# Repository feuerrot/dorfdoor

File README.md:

# Türsteuerung
Can haz digitale Türsteuerung mit verschiedenen Inputs und Statusleds und
foo? Ja!

Die [Tür des Chaosdorf](https://wiki.chaosdorf.de/Chaosdoor) hat einen 
eingebauten Motor von Fuhr - den Multitronic 881 und da alle Funkanwendungen
(insbesondere der Funk-Fingerabdrucksensor) auf unbekannter Technik basieren
und damit erstmal als für einen Hackerspace ungeeignet gelten, muss man das
natürlich selber bauen.

## History
v1 umfasste eine Lochrasterplatine mit AVR ATMega8, der über Optokoppler den
Potentialfreien Eingang des Türmotors ansteuerte. Ein Problem war unter
anderem, dass der komplette Öffnungs- und Schließvorgang incl. Verriegeln
dazu führte, dass nach gerade mal 3 Jahren ein Zahnrad brach.

Die aktuelle v2 mit 'lag halt rum' AVR ATMega88PA trennt eigentliche
Steuerung und Boardinterface auf zwei Platinen auf. Der Mikrocontroller ist
zusammen mit der verbundenen Seagate Dockstar und passendem Netzteil für
alles und Tür in einem Gehäuse. Die Ansteuerung der Tür und das damit
verbundene Problem bleibt bestehen.

[@penma](https://github.com/penma) hat aber dankenswerterweise das
Protokoll der Tür im für unseren Zweck ausreichenden Maße reverse
engineered, um die gewünschte Tagesfallenfunktion auch ohne Zusatzplatine
für wahrscheinlich mehrere hunderte Euro zu erlangen.
Bei v2 wird dafür der Optokoppler für die Tagesfalle genutzt.

## Schaltplan

### μC-Platine

### IO-Platine

## Layout

### μC-Platine

### IO-Platine

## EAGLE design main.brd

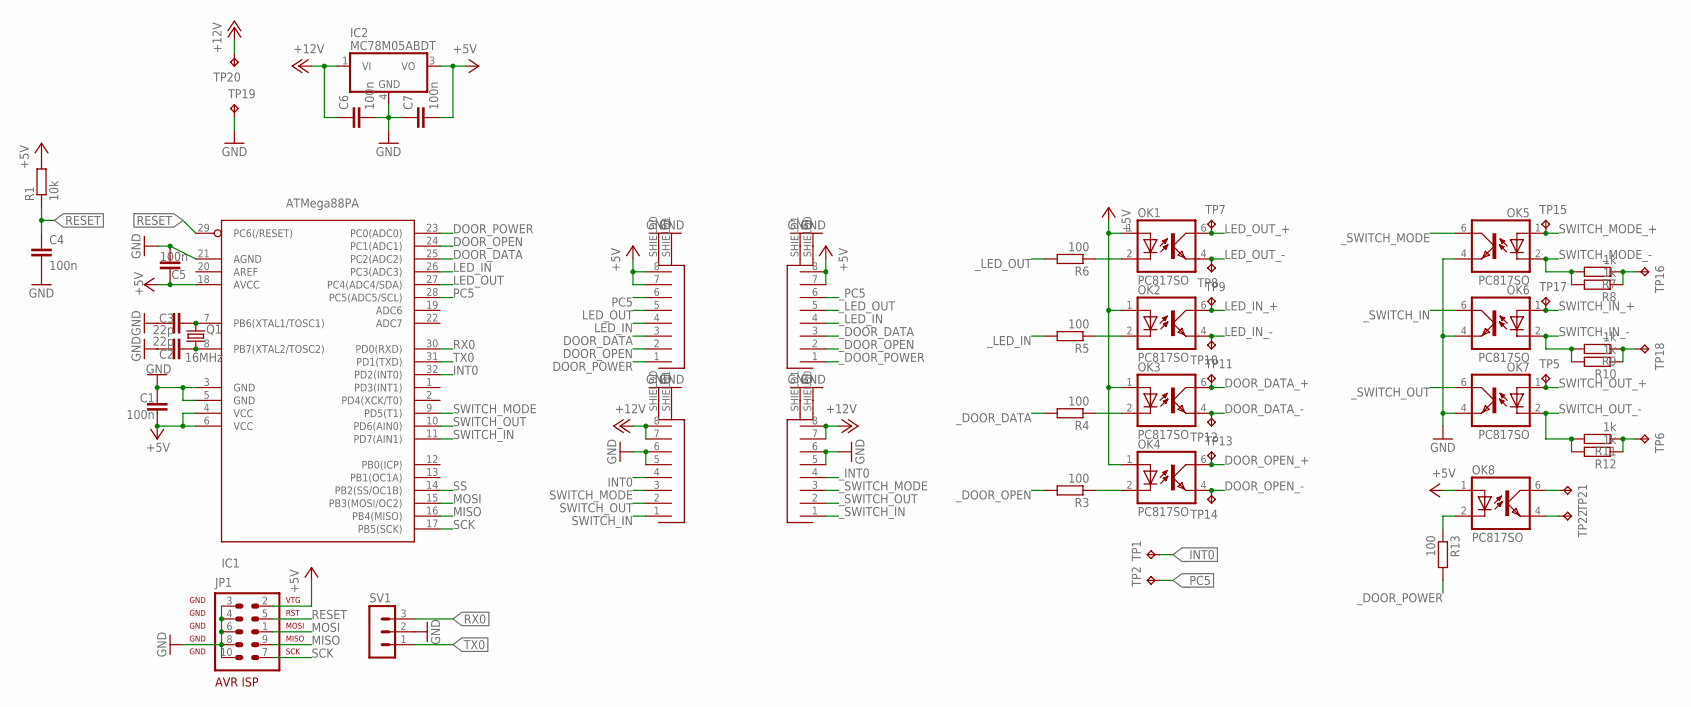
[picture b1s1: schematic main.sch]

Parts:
C1, C4, C5, C6, C7: 100n; C0805
C2, C3: 22p; C0805
CON1, CON1_, CON2, CON2_: 451000
IC1: ATMega88PA; TQFP32-08
IC2: MC78M05ABDT; DPACK_3
JP1: AVR-ISP-10
OK1, OK2, OK3, OK4, OK5, OK6, OK7, OK8: PC817SO; SO4
Q1: 16MHz; MQ
R1: 10k; M0805
R3, R4, R5, R6, R13: 100; M0805
R7, R8, R9, R10, R11, R12: 1k; M0805
SV1: MA03-1
TP1, TP2, TP5, TP6, TP7, TP8, TP9, TP10, TP11, TP12, TP13, TP14, TP15, TP16, TP17, TP18, TP19, TP20, TP21, TP22: TPTP20SQ; TP20SQ

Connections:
+5V: C1.1, C5.1, C7.2, CON2.7, CON2.8, CON2_.7, CON2_.8, IC1.4 (VCC), IC1.6 (VCC), IC1.18 (AVCC), IC2.3 (VO), JP1.2, OK1.1 (A), OK2.1 (A), OK3.1 (A), OK4.1 (A), OK8.1 (A), R1.2
+12V: C6.1, CON1.7, CON1.8, CON1_.7, CON1_.8, IC2.1 (VI), TP20.TP
DOOR_DATA: CON2.3, IC1.25 (PC2(ADC2))
DOOR_DATA_+: OK3.6 (COL), TP11.TP
DOOR_DATA_-: OK3.4 (EMIT), TP12.TP
DOOR_OPEN: CON2.2, IC1.24 (PC1(ADC1))
DOOR_OPEN_+: OK4.6 (COL), TP13.TP
DOOR_OPEN_-: OK4.4 (EMIT), TP14.TP
DOOR_POWER: CON2.1, IC1.23 (PC0(ADC0))
GND: C1.2, C2.1, C3.1, C4.2, C5.2, C6.2, C7.1, CON1.5, CON1.6, CON1.SHIELD0, CON1.SHIELD1, CON1_.5, CON1_.6, CON1_.SHIELD0, CON1_.SHIELD1, CON2.SHIELD0, CON2.SHIELD1, CON2_.SHIELD0, CON2_.SHIELD1, IC1.3 (GND), IC1.5 (GND), IC1.21 (AGND), IC2.4 (GND), JP1.3, JP1.4, JP1.6, JP1.8, JP1.10, OK5.4 (EMIT), OK6.4 (EMIT), OK7.4 (EMIT), SV1.2, TP19.TP
INT0: CON1.4, IC1.32 (PD2(INT0))
LED_IN: CON2.4, IC1.26 (PC3(ADC3))
LED_IN_+: OK2.6 (COL), TP9.TP
LED_IN_-: OK2.4 (EMIT), TP10.TP
LED_OUT: CON2.5, IC1.27 (PC4(ADC4/SDA))
LED_OUT_+: OK1.6 (COL), TP7.TP
LED_OUT_-: OK1.4 (EMIT), TP8.TP
MISO: IC1.16 (PB4(MISO)), JP1.9
MOSI: IC1.15 (PB3(MOSI/OC2)), JP1.1
unnamed: OK8.2 (C), R13.1
unnamed: OK4.2 (C), R3.1
unnamed: C3.2, IC1.7 (PB6(XTAL1/TOSC1)), Q1.P3 (2)
unnamed: C2.2, IC1.8 (PB7(XTAL2/TOSC2)), Q1.P1 (1)
unnamed: OK3.2 (C), R4.1
unnamed: OK2.2 (C), R5.1
unnamed: OK1.2 (C), R6.1
unnamed: R7.1, R8.1, TP16.TP
unnamed: R11.1, R12.1, TP6.TP
unnamed: R9.1, R10.1, TP18.TP
unnamed: OK8.6 (COL), TP21.TP
unnamed: OK8.4 (EMIT), TP22.TP
PC5: CON2.6, IC1.28 (PC5(ADC5/SCL))
RESET: C4.1, IC1.29 (PC6(/RESET)), JP1.5, R1.1
RX0: IC1.30 (PD0(RXD)), SV1.3
SCK: IC1.17 (PB5(SCK)), JP1.7
SS: IC1.14 (PB2(SS/OC1B))
SWITCH_IN: CON1.1, IC1.11 (PD7(AIN1))
SWITCH_IN_+: OK6.1 (A), TP17.TP
SWITCH_IN_-: OK6.2 (C), R9.2, R10.2
SWITCH_MODE: CON1.3, IC1.9 (PD5(T1))
SWITCH_MODE_+: OK5.1 (A), TP15.TP
SWITCH_MODE_-: OK5.2 (C), R7.2, R8.2
SWITCH_OUT: CON1.2, IC1.10 (PD6(AIN0))
SWITCH_OUT_+: OK7.1 (A), TP5.TP
SWITCH_OUT_-: OK7.2 (C), R11.2, R12.2
TX0: IC1.31 (PD1(TXD)), SV1.1
_DOOR_DATA: CON2_.3, R4.2
_DOOR_OPEN: CON2_.2, R3.2
_DOOR_POWER: CON2_.1, R13.2
_INT0: CON1_.4, TP1.TP
_LED_IN: CON2_.4, R5.2
_LED_OUT: CON2_.5, R6.2
_PC5: CON2_.6, TP2.TP
_SWITCH_IN: CON1_.1, OK6.6 (COL)
_SWITCH_MODE: CON1_.3, OK5.6 (COL)
_SWITCH_OUT: CON1_.2, OK7.6 (COL)

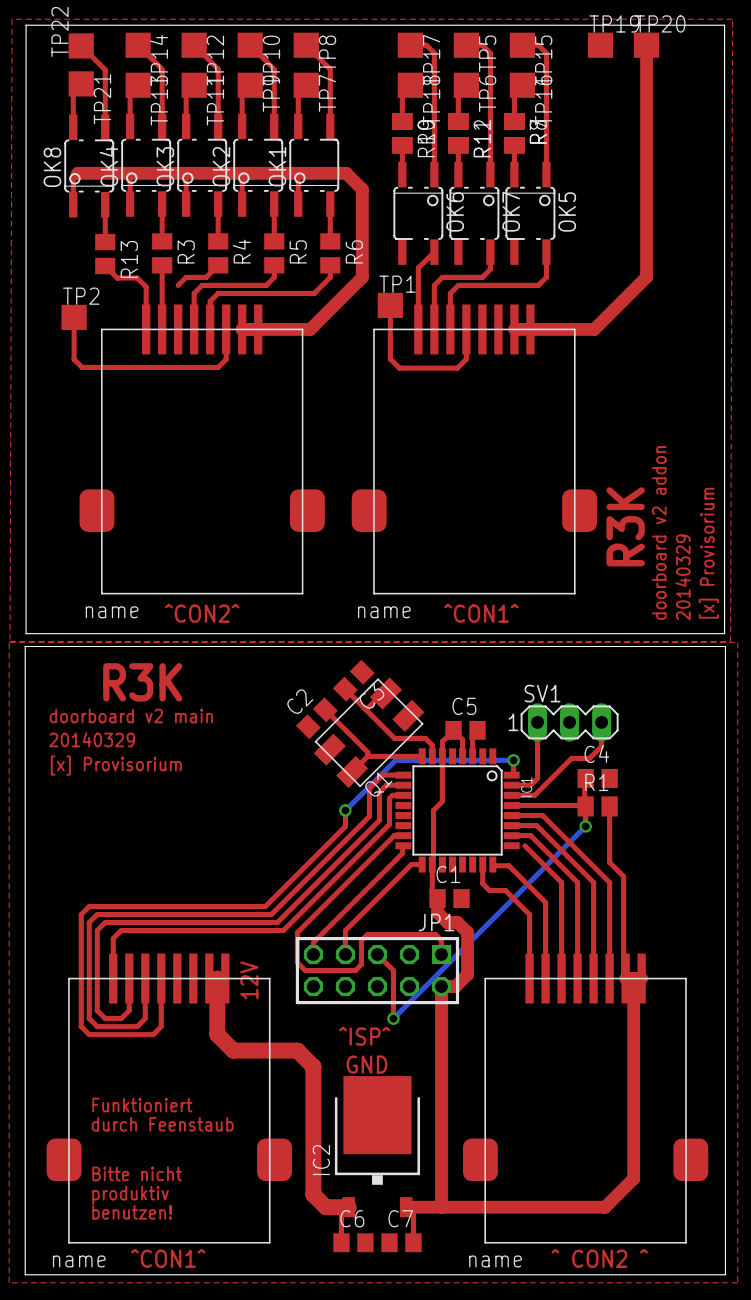
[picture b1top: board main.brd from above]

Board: 2 copper layers, 55.5 x 99.1 mm, 56 parts (0 on the bottom side), 55 nets.

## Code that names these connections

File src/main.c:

// coding: utf-8
#include <avr/io.h>
#include <avr/interrupt.h>
#include <avr/wdt.h>
#include <util/delay.h>
#include "rs232.h"

char resettext[]	=	"p";	// power on
char openhs[]		=	"o";	// hackerspace open
char closedhs[]		=	"c";	// hackerspace closed
char dooror1[]		=	"1";	// ssh stage 1
char dooror2[]		=	"2";	// ssh stage 2
char dooror3[]		=	"e";	// ssh error
char dooropened[]	=	"s";	// open via switch
char bell[]		=	"b";	// bell
char resetof[]		=	"r";	// ssh stage reset
char statuso[]		=	"SO";
char statusc[]		=	"SC";

volatile uint8_t resetoverflow;
uint8_t toggledoor;
#define DOORTOGGLE 20

#define SWITCH_RED	PD2 // Taster Rot
#define SWITCH_GREEN	PD5 // Taster Grün
#define SWITCH_OUT	PD6
#define SWITCH_IN	PD7
#define DOOR_DATA	PC2
#define DOOR_POWER	PC0
#define DOOR_OPEN	PC1
#define LED_OUT		PC4 // normale LED im Außentaster
#define LED_IN		PC3 // sind die WS2812b

volatile struct {
	unsigned dooropenstage1:1;
	unsigned dooropenstage2:1;
	unsigned openhackerspace:1;
	unsigned openhackerspaceold:1;
	unsigned bell:1;
} flags;

#define CMD_OPEN_LOCK      0x10cd
#define CMD_OPEN_TF        0x11d0
#define CMD_OPEN_TF_HOLD   0x12f7
#define CMD_LOCK           0x14b9
#define CMD_UNLOCK         0x179e

void ws2812bit(uint8_t bit){
	PORTC |= (1<<LED_IN);
	if (bit){
		_delay_us(0.85);
		PORTC &= ~(1<<LED_IN);
		_delay_us(0.35);
	} else {
		_delay_us(0.35);
		PORTC &= ~(1<<LED_IN);
		_delay_us(0.85);
	}
}

void led_r(void){
	for (int i=7; i>=0; i--){
		ws2812bit(0);
	}
	for (int i=7; i>=0; i--){
		ws2812bit(1);
	}
	for (int i=7; i>=0; i--){
		ws2812bit(0);
	}
}

void led_g(void){
	for (int i=7; i>=0; i--){
		ws2812bit(1);
	}
	for (int i=13; i>=0; i--){
		ws2812bit(0);
	}
}


static void send_door_halfbit(int v) {
	if (!v) {
		PORTC &= ~(1 << DOOR_DATA);
	} else {
		PORTC |= (1 << DOOR_DATA);
	}
	_delay_us(500);
}

static void send_door_cmd(uint16_t word) {
	cli();

	for (int rep = 1; rep <= 11; rep++) {
		send_door_halfbit(0);

		for (signed int i = 15; i >= 0; i--) {
			if (word & ((uint16_t)1 << i)) {
				/* bit set */
				send_door_halfbit(1);
				send_door_halfbit(0);
			} else {
				send_door_halfbit(0);
				send_door_halfbit(1);
			}
		}

		/* release bus */
		send_door_halfbit(1);

		/* packet delay */
		_delay_us(2500);
	}

	sei();
}

void setled(uint8_t led){
	cli();
	if (led){
		PORTC &= ~(1<<LED_OUT);
		led_g();
		led_g();
		led_g();
	} else {
		PORTC |= (1<<LED_OUT);
		led_r();
		led_r();
		led_r();
	}
	sei();
}

void opendoor(void){
	if (flags.openhackerspace) {
		send_door_cmd(CMD_OPEN_TF);
	} else {
		send_door_cmd(CMD_OPEN_LOCK);
	}
	_delay_ms(100);
	_serputs(dooropened);
}

uint8_t input(uint8_t flag){
	return (!(PIND & (1<<flag)));
}

void init(void){
	_usart_init();

	/* Protipp:
	 * Der Defaultzustand von PORT- und DDR-Registern ist 0x00.
	 * D.h.: Schaltfunktion bei Output = low ist eine scheiß Idee.
	 *
	 * Hier fixen wir das, indem wir erstmal einen Pullup machen und
	 * dann den Pin auf high schalten.
	 */
	PORTC |= (1<<DOOR_OPEN);
	DDRC  |= (1<<DOOR_OPEN);

	DDRC  |= (1<<DOOR_DATA)|(1<<DOOR_POWER)|(1<<LED_OUT)|(1<<LED_IN);
	PORTC |= (1<<DOOR_DATA)|(1<<LED_OUT)|(1<<LED_IN);

	PORTD |= (1<<SWITCH_GREEN)|(1<<SWITCH_RED)|(1<<SWITCH_OUT)|(1<<SWITCH_IN);

	_delay_ms(10);
	TCCR2B |= (1<<CS22)|(1<<CS21);
	TIMSK2 |= (1<<TOIE2);

	setled(0);

	sei();
	_serputs(resettext);
}

int main(void) {
	init();

	while(1) {
		if (flags.openhackerspace != flags.openhackerspaceold){
			flags.openhackerspaceold = flags.openhackerspace;
			if (flags.openhackerspace){
				send_door_cmd(CMD_UNLOCK);
				setled(1);
				_serputs(openhs);
			} else {
				send_door_cmd(CMD_LOCK);
				setled(0);
				_serputs(closedhs);
			}
		}
		if (flags.openhackerspace){
			if (input(SWITCH_IN) | input(SWITCH_OUT)){
				setled(0);
				_delay_ms(50);
				setled(1);
				opendoor();
				setled(0);
				_delay_ms(50);
				setled(1);
			}
		} else {
			if ((input(SWITCH_IN) | input(SWITCH_OUT)) && flags.bell == 0){
				_serputs(bell);
				flags.bell = 1;
				//Klingelfunktion
			}
		}
		if (flags.dooropenstage2){
			_serputs(dooror2);
			flags.dooropenstage2 = 0;
			opendoor();
		}

		if (input(SWITCH_GREEN)|input(SWITCH_RED)){
			toggledoor++;
		} else {
			toggledoor = 0;
		}
		if (toggledoor > DOORTOGGLE){
			if ((flags.openhackerspace == 0 && input(SWITCH_GREEN))||(flags.openhackerspace == 1 && input(SWITCH_RED))){
				flags.openhackerspace ^= 1;
			}
			toggledoor = 0;
		}

		_delay_ms(100);
	}
	return 0;
}

ISR(USART_RX_vect){
    uint8_t chr = UDR0;
    switch (chr){
		case 'r':
		       	wdt_enable(WDTO_1S);
			break;
		case 'd':
			if (flags.dooropenstage1){
				_serputs(dooror3);
			} else {
				flags.dooropenstage1 = 1;
				_serputs(dooror1);
			}
			break;
		case 'b':
			if (flags.dooropenstage1){
				flags.dooropenstage2 = 1;
				flags.dooropenstage1 = 0;
			} else {
				_serputs(dooror3);
			}
			break;
		case 'o':
			flags.openhackerspace = 1;
			break;
		case 'c':
			flags.openhackerspace = 0;
			break;
		case 's':
			if (flags.openhackerspace){
				_serputs(statuso);
			} else {
				_serputs(statusc);
			}
		default:
			flags.dooropenstage1 = 0;
			break;
    }
}

ISR(TIMER2_OVF_vect){
	if (resetoverflow == 0){
		flags.dooropenstage1 = 0;
		flags.dooropenstage2 = 0;
		flags.bell = 0;
		_serputs(resetof);
	}
	resetoverflow++;
}

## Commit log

2012-03-31 Rückmeldungen auf ein Zeichen angepasst, aber noch mit \n
    Muss noch schöner werden und so…
2012-04-01 Manuelle Steuerung über Taster eingebaut
    * 2 Sekunden drücken zum togglen des Status (auf<->zu)
    * Der Code ist immernoch weird
    * Andere LEDs ausmachen, dass nur eine leuchtet oder alle zusammen leuchten?
    * Pythonscript, das auf dem host läuft mit rein.
2012-04-02 Alle LEDs ändern ihren Status
    Da derzeit nur eine LED genutzt wird, zeigen die anderen LEDs genau das
    gleiche an, um Nutzer nach einer Änderung zu verwirren.
2012-04-04 Der Host kann nun den aktuellen Status abfragen
2014-09-27 Uralten code anfassen \o/
2014-09-28 what? ahrgs, das ist ja grottig. Alles neu schreiben…
2014-09-29 scheiß code, funktioniert aber inzwischen
2014-10-04 updating gitignore
2014-10-04 add layout and schematic
2014-10-04 add fuse settings and program-fuse to makefile
2014-10-04 added a readme
2014-10-04 adding images of the current version
2014-10-04 Optokoppler für Daymode => Optokoppler für Datenleitung
2014-10-04 :%s/DOOR_DAYMODE/DOOR_DATA/g
2014-10-04 DOOR_DAYMODE => DOOR_DATA jetzt auch im Schaltplan
2014-10-04 @penma hackte
2014-10-09 gehäuse für die modusbuttons
2014-10-09 aufhängefoo für das Gehäuse
2014-10-09 jetzt auch als ein Teil
2014-10-09 jetzt auch mit stützfoo
2014-10-11 ws2812b dreckig und hoffentlich funktionierend einbinden
2014-10-11 Da sind 3 Leds drin und nicht nur eine.
2014-10-11 + cli();sei(); um die LED-Ansteuerung, weil timing
2014-10-11 s/SWITCH_MODE/SWITCH_GREEN/ und beide Taster eingebaut
2014-10-13 set led on powerup
